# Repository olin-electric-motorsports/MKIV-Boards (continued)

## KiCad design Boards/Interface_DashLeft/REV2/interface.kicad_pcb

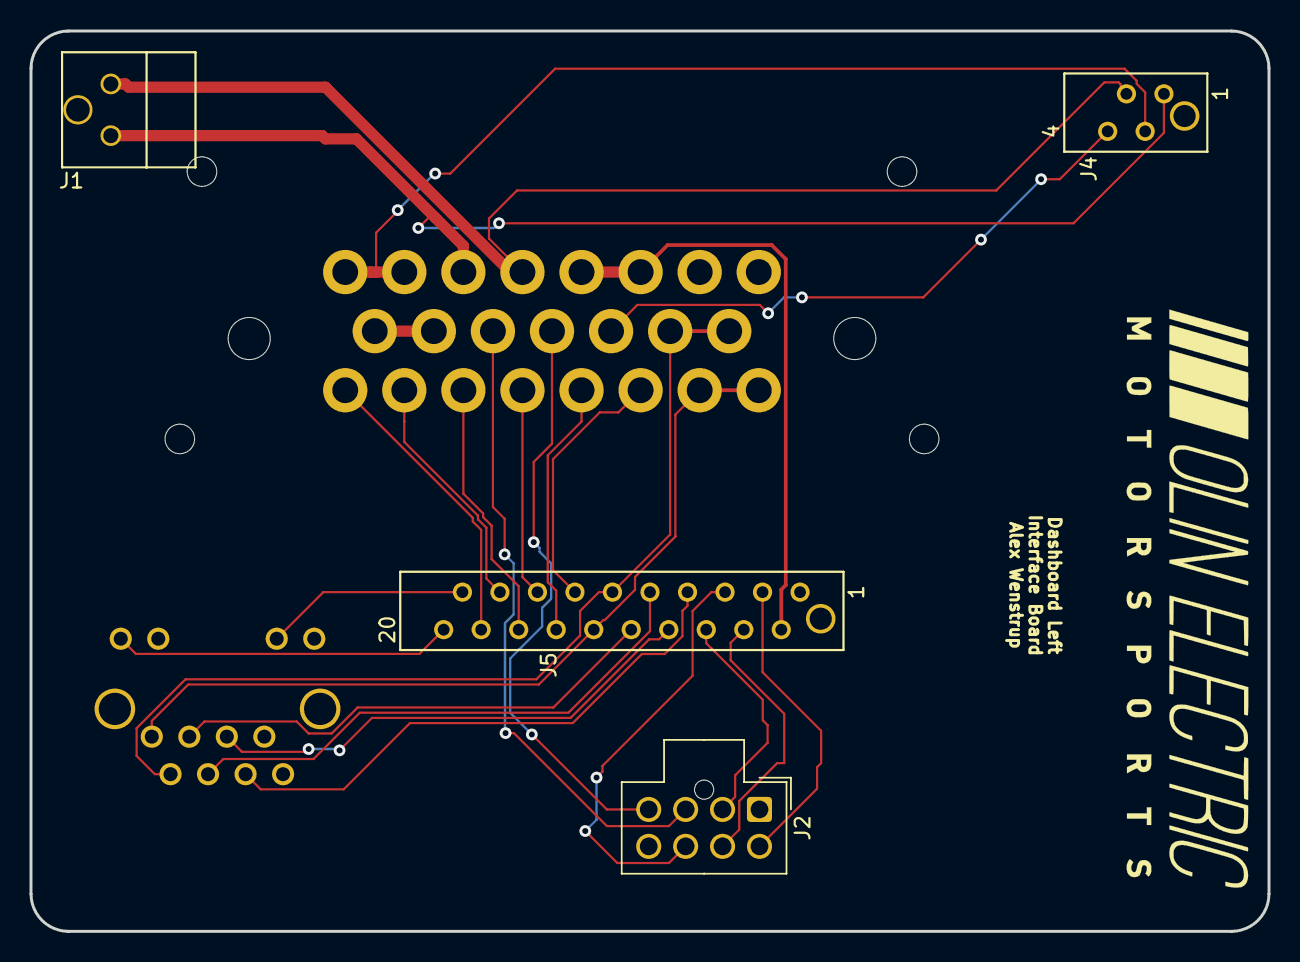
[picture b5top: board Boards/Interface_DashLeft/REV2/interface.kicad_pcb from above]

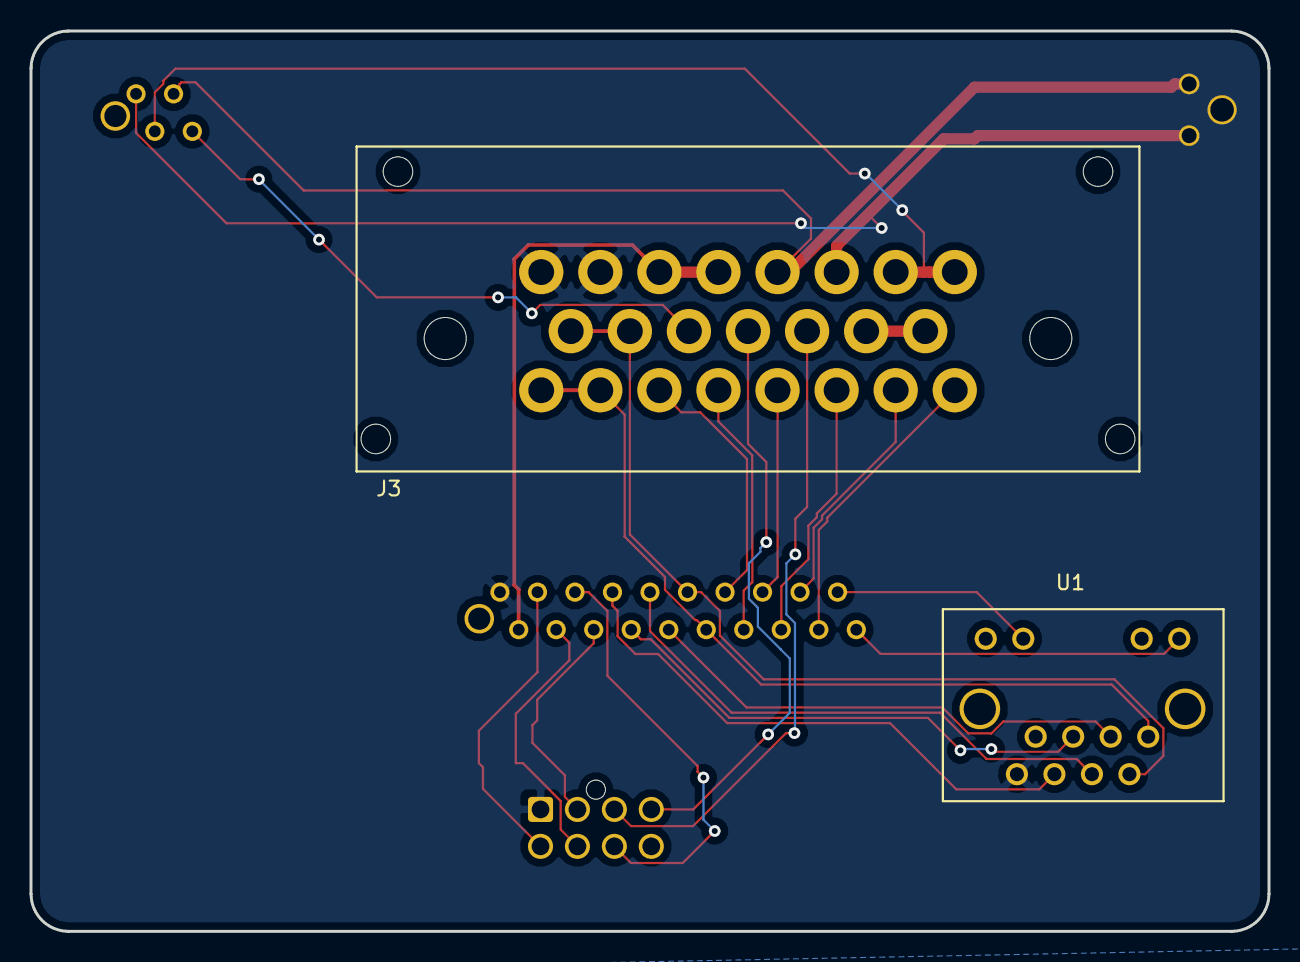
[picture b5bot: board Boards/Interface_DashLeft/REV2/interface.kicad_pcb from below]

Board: 2 copper layers, 83.8 x 61.0 mm, 6 parts (2 on the bottom side), 27 nets.

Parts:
J1: UF_2_VT; Ultrafit_2
J2: MM_F_VT_08; Molex_Nano-Fit_105310-xx08_2x04_P2.50mm_Vertical
J3: Ampseal_23_VT; Ampseal_23
J4: MM_F_VT_04; micromatch_female_vert_4
J5: MM_F_VT_20; micromatch_female_vert_20
U1: RJ45_VT; RJ45-Vertical

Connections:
/5V: J2.2, J5.6
/12V: J3.3, J3.4, J5.2
/BOTS->ESTOP: J1.2, J3.6, J4.1
/BSPD->IS: J3.14, J3.15
/CANH: J3.9, J3.10, J5.11, U1.2
/CANL: J3.16, J3.17, J5.12, U1.1
/Drive_Select+: J2.5, J5.3
/Drive_Select-: J2.7, J5.5
/Drive_Select_Sense: J2.6, J5.4
/ESTOP->HVD: J1.1, J3.5, J4.3
/GND: J2.1, J3.1, J3.2, J5.1, U1.8
/IS->BOTS: J3.7, J3.8, J4.2
/LED1: J5.19, U1.10
/LED2: J5.20, U1.12
/MISO: J5.8, U1.5
/MOSI: J5.7, U1.6
/RESET: J5.10, U1.3
/RTD_LSD_GND: J3.11, J4.4
/SCK: J5.9, U1.4
/SCL: J2.4, J3.12
/SDA: J2.3, J3.13
/Throttle1+: J3.18, J5.13
/Throttle1-: J3.20, J5.15
/Throttle1_Sense: J3.19, J5.14
/Throttle2+: J3.21, J5.16
/Throttle2-: J3.23, J5.18
/Throttle2_Sense: J3.22, J5.17

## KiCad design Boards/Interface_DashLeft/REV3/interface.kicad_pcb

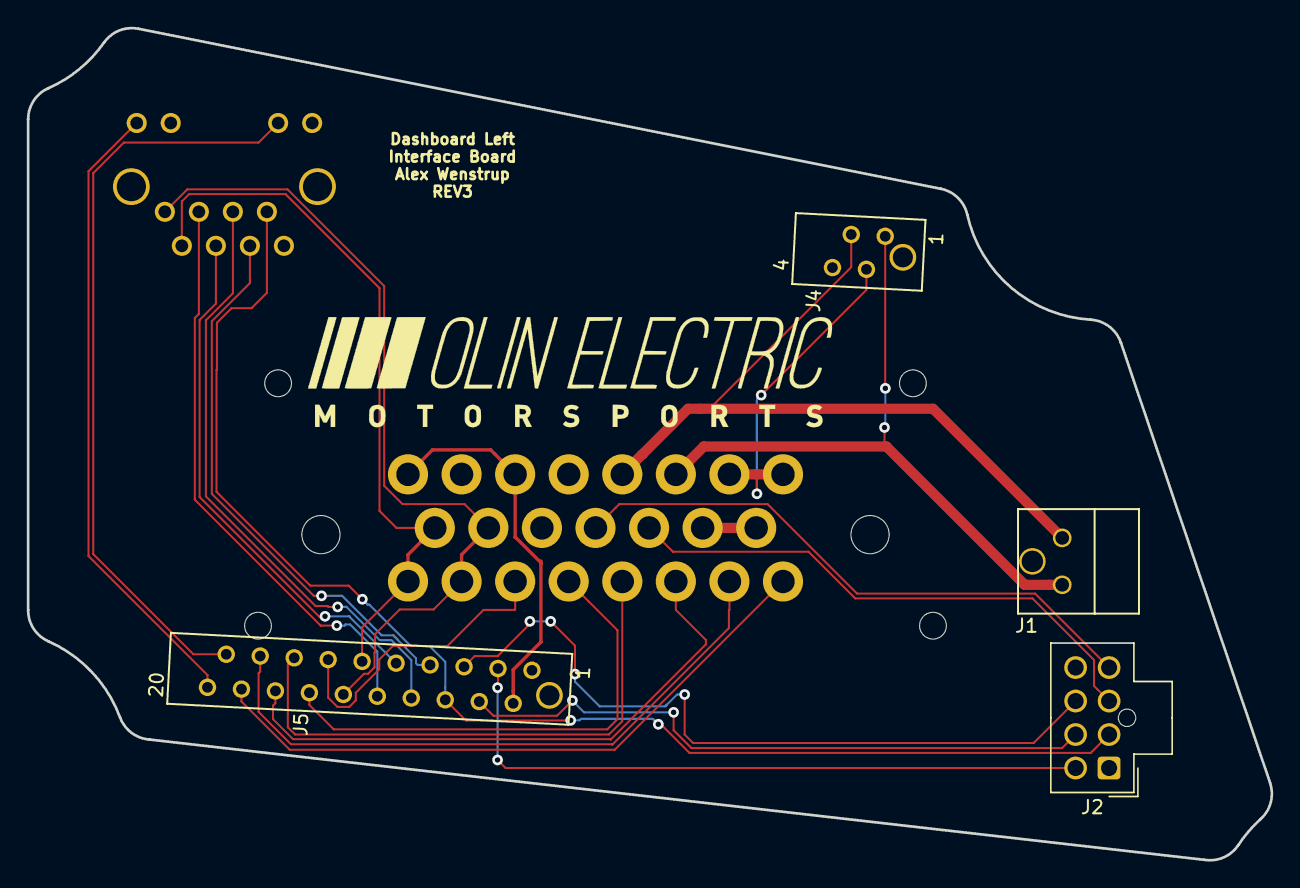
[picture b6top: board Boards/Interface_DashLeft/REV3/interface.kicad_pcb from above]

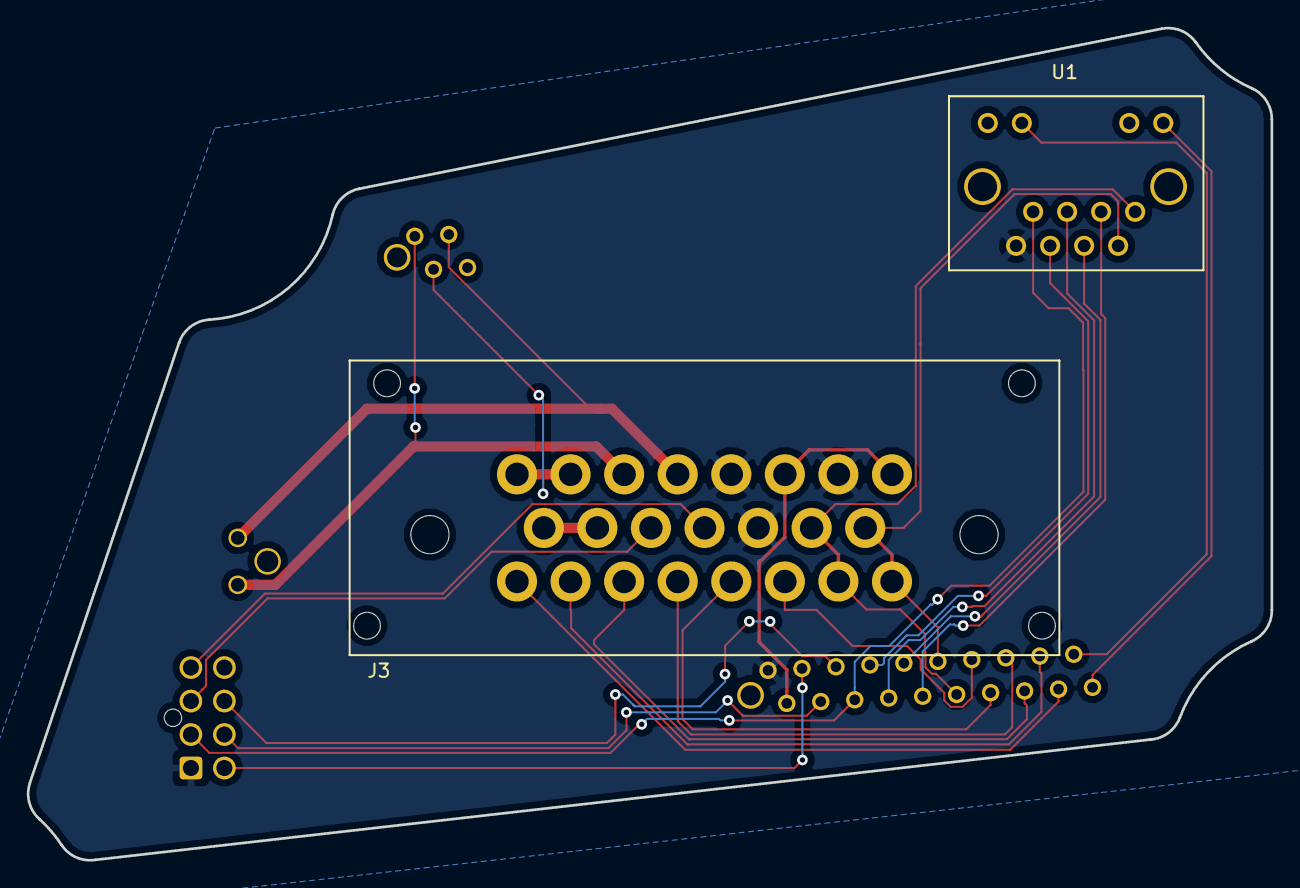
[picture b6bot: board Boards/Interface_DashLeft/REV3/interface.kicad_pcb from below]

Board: 2 copper layers, 92.9 x 62.1 mm, 6 parts (2 on the bottom side), 26 nets.

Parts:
J1: UF_2_VT; Ultrafit_2
J2: MM_F_VT_08; Molex_Nano-Fit_105310-xx08_2x04_P2.50mm_Vertical
J3: Ampseal_23_VT; Ampseal_23
J4: MM_F_VT_04; micromatch_female_vert_4
J5: MM_F_VT_20; micromatch_female_vert_20
U1: RJ45_VT; RJ45-Vertical

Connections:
/5V: J2.2, J5.6, U1.7
/12V: J3.6, J3.8, J5.2
/BOTS->ESTOP: J1.2, J3.3, J4.1
/BSPD->IS: J3.9, J3.10
/CANH: J3.15, J3.23, J5.11, U1.2
/CANL: J3.14, J3.22, J5.12, U1.1
/Drive_Select+: J2.5, J5.3
/Drive_Select-: J2.7, J5.5
/Drive_Select_Sense: J2.6, J5.4
/ESTOP->HVD: J1.1, J3.4, J4.3
/GND: J2.1, J3.5, J3.7, J3.13, J5.1, U1.8
/IS->BOTS: J3.1, J3.2, J4.2
/LED1: J5.19, U1.10
/LED2: J5.20, U1.12
/MISO: J5.8, U1.5
/MOSI: J5.7, U1.6
/RESET: J5.10, U1.3
/SCK: J5.9, U1.4
/SCL: J2.4, J3.12
/SDA: J2.3, J3.11
/Throttle1+: J3.21, J5.13
/Throttle1-: J3.19, J5.15
/Throttle1_Sense: J3.20, J5.14
/Throttle2+: J3.18, J5.16
/Throttle2-: J3.16, J5.18
/Throttle2_Sense: J3.17, J5.17
